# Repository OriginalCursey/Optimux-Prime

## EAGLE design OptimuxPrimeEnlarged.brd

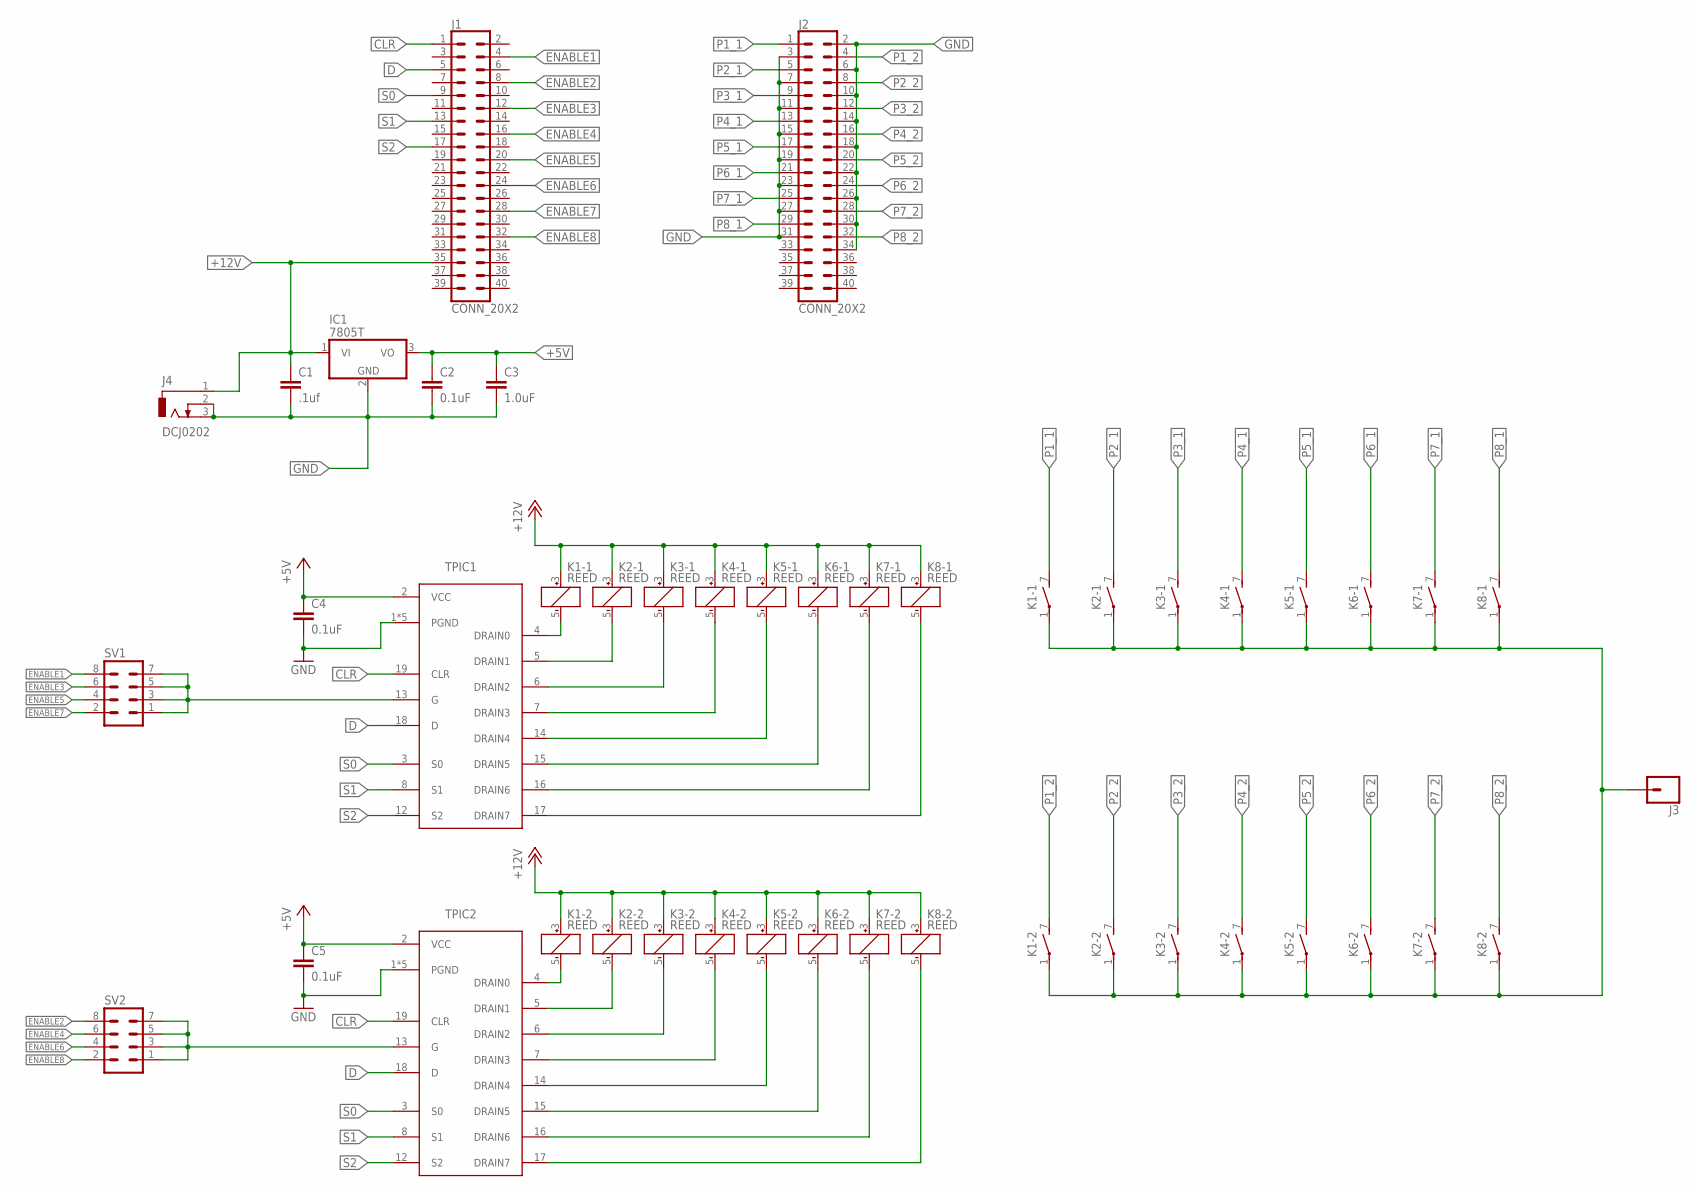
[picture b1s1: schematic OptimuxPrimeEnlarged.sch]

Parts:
C1: .1uf; 0805
C2, C4, C5: 0.1uF; 0805
C3: 1.0uF; 0805
IC1: 7805T; TO220H
J1, J2: CONN_20X2; 2X20
J3: CONN_01; 1X01
J4: DCJ0202
K1-1, K1-2, K2-1, K2-2, K3-1, K3-2, K4-1, K4-2, K5-1, K5-2, K6-1, K6-2, K7-1, K7-2, K8-1, K8-2: REED
SV1, SV2: MA04-2
TPIC1, TPIC2: TPIC6259; DIL20

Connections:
+5V: C2.1, C3.1, C4.1, C5.1, IC1.3 (VO), TPIC1.2 (VCC), TPIC2.2 (VCC)
+12V: C1.1, IC1.1 (VI), J1.35, J4.1, K1-1.3 (+), K1-2.3 (+), K2-1.3 (+), K2-2.3 (+), K3-1.3 (+), K3-2.3 (+), K4-1.3 (+), K4-2.3 (+), K5-1.3 (+), K5-2.3 (+), K6-1.3 (+), K6-2.3 (+), K7-1.3 (+), K7-2.3 (+), K8-1.3 (+), K8-2.3 (+)
CLR: J1.1, TPIC1.19 (CLR), TPIC2.19 (CLR)
D: J1.5, TPIC1.18 (D), TPIC2.18 (D)
ENABLE1: J1.4, SV1.8
ENABLE2: J1.8, SV2.8
ENABLE3: J1.12, SV1.6
ENABLE4: J1.16, SV2.6
ENABLE5: J1.20, SV1.4
ENABLE6: J1.24, SV2.4
ENABLE7: J1.28, SV1.2
ENABLE8: J1.32, SV2.2
GND: C1.2, C2.2, C3.2, C4.2, C5.2, IC1.2 (GND), J2.2, J2.3, J2.6, J2.7, J2.10, J2.11, J2.14, J2.15, J2.18, J2.19, J2.22, J2.23, J2.26, J2.27, J2.30, J2.31, J2.34, J4.2, J4.3, TPIC1.1 (PGND), TPIC1.9 (PGND), TPIC1.10 (PGND), TPIC1.11 (PGND), TPIC1.20 (PGND), TPIC2.1 (PGND), TPIC2.9 (PGND), TPIC2.10 (PGND), TPIC2.11 (PGND), TPIC2.20 (PGND)
unnamed: K1-1.5 (-), TPIC1.4 (DRAIN0)
unnamed: K2-1.5 (-), TPIC1.5 (DRAIN1)
unnamed: K3-1.5 (-), TPIC1.6 (DRAIN2)
unnamed: K4-1.5 (-), TPIC1.7 (DRAIN3)
unnamed: K5-1.5 (-), TPIC1.14 (DRAIN4)
unnamed: K6-1.5 (-), TPIC1.15 (DRAIN5)
unnamed: K7-1.5 (-), TPIC1.16 (DRAIN6)
unnamed: K8-1.5 (-), TPIC1.17 (DRAIN7)
unnamed: SV1.1, SV1.3, SV1.5, SV1.7, TPIC1.13 (G)
unnamed: SV2.1, SV2.3, SV2.5, SV2.7, TPIC2.13 (G)
unnamed: K1-2.5 (-), TPIC2.4 (DRAIN0)
unnamed: K2-2.5 (-), TPIC2.5 (DRAIN1)
unnamed: K3-2.5 (-), TPIC2.6 (DRAIN2)
unnamed: K4-2.5 (-), TPIC2.7 (DRAIN3)
unnamed: K5-2.5 (-), TPIC2.14 (DRAIN4)
unnamed: K6-2.5 (-), TPIC2.15 (DRAIN5)
unnamed: K7-2.5 (-), TPIC2.16 (DRAIN6)
unnamed: K8-2.5 (-), TPIC2.17 (DRAIN7)
P1_1: J2.1, K1-1.7 (S)
P1_2: J2.4, K1-2.7 (S)
P2_1: J2.5, K2-1.7 (S)
P2_2: J2.8, K2-2.7 (S)
P3_1: J2.9, K3-1.7 (S)
P3_2: J2.12, K3-2.7 (S)
P4_1: J2.13, K4-1.7 (S)
P4_2: J2.16, K4-2.7 (S)
P5_1: J2.17, K5-1.7 (S)
P5_2: J2.20, K5-2.7 (S)
P6_1: J2.21, K6-1.7 (S)
P6_2: J2.24, K6-2.7 (S)
P7_1: J2.25, K7-1.7 (S)
P7_2: J2.28, K7-2.7 (S)
P8_1: J2.29, K8-1.7 (S)
P8_2: J2.32, K8-2.7 (S)
S0: J1.9, TPIC1.3 (S0), TPIC2.3 (S0)
S1: J1.13, TPIC1.8 (S1), TPIC2.8 (S1)
S2: J1.17, TPIC1.12 (S2), TPIC2.12 (S2)
SCOPE_OUT: J3.1, K1-1.1, K1-2.1, K2-1.1, K2-2.1, K3-1.1, K3-2.1, K4-1.1, K4-2.1, K5-1.1, K5-2.1, K6-1.1, K6-2.1, K7-1.1, K7-2.1, K8-1.1, K8-2.1

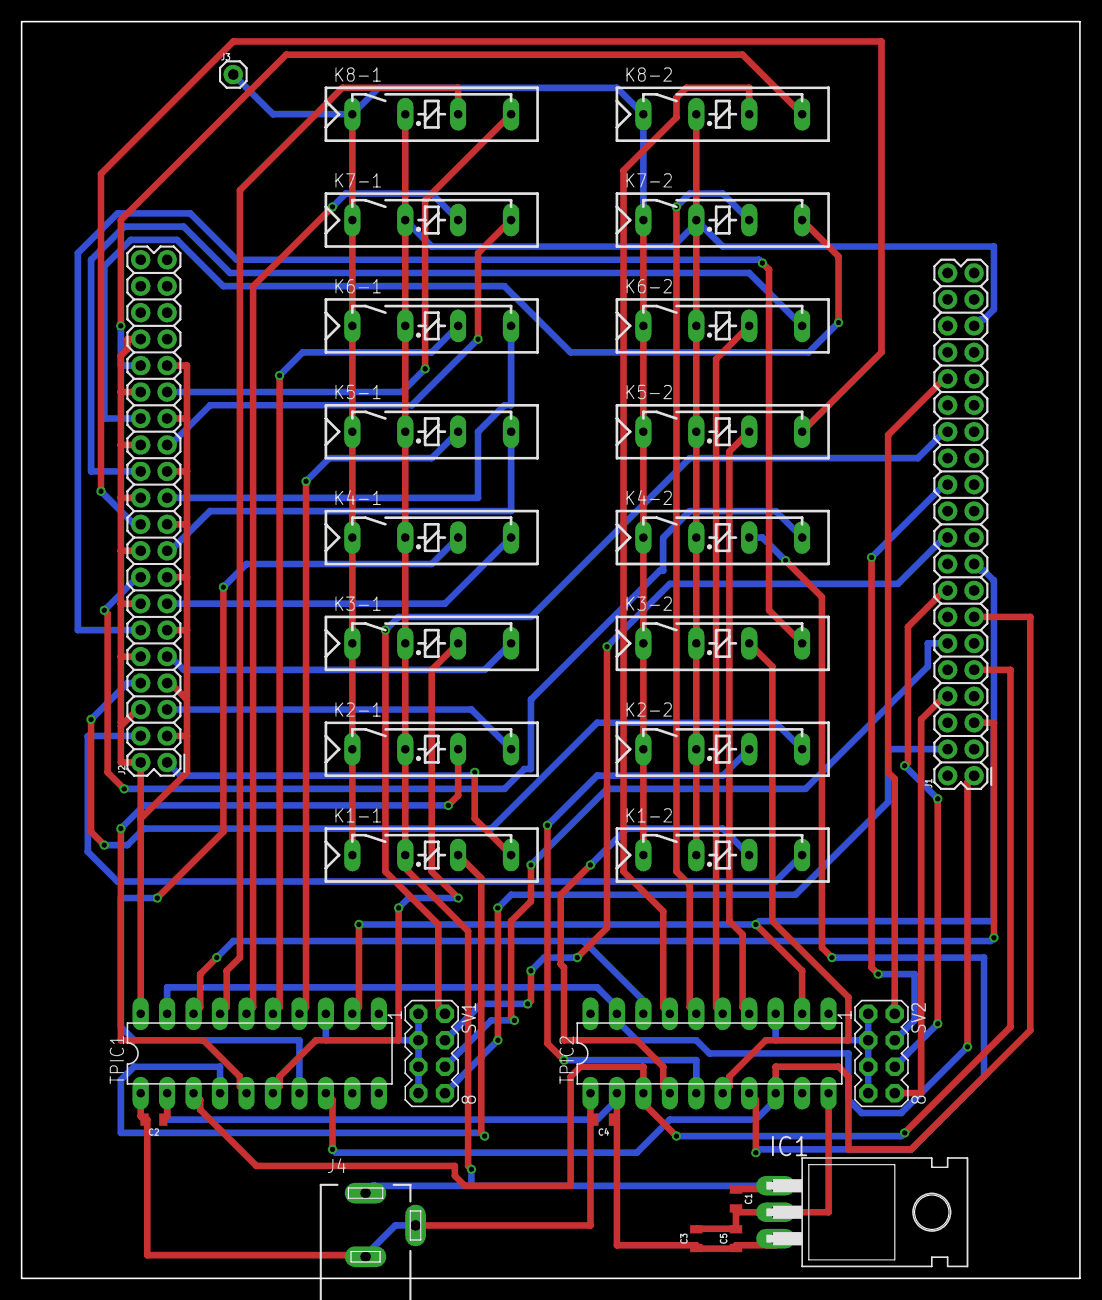
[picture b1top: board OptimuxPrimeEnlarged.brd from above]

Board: 2 copper layers, 101.6 x 120.7 mm, 30 parts (0 on the bottom side), 51 nets.

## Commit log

2017-10-08 Uploaded board schematics and layout
2017-12-11 Added enlarged board schematic and fixed board schematic
2017-12-11 added pdf
2017-12-11 ThermonicsNozzle Layout
2017-12-13 sprocket gcode

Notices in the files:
parts and their libraries:
SparkFun-Capacitors: Licensing: Creative Commons ShareAlike 4.0 International - https://creativecommons.org/licenses/by-sa/4.0
